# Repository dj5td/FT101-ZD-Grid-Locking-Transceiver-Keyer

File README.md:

# FT101-ZD-Grid-Locking-Transceiver-Keyer

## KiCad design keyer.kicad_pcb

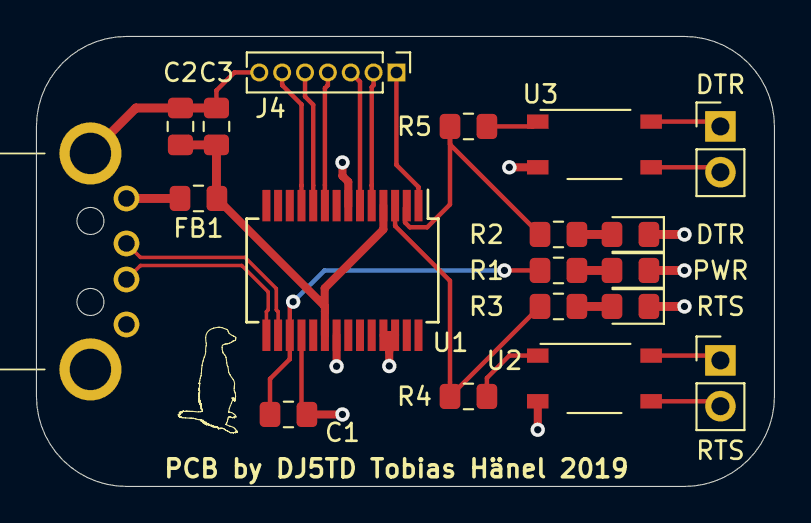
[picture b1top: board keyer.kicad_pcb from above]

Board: 2 copper layers, 41.0 x 25.0 mm, 19 parts (0 on the bottom side), 23 nets.

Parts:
C1, C2: 100nF; C_0805_2012Metric_Pad1.15x1.40mm_HandSolder
C3: 10 uF; C_0805_2012Metric_Pad1.15x1.40mm_HandSolder
DTR: LED; LED_0805_2012Metric_Pad1.15x1.40mm_HandSolder
DTR#2: Conn_Coaxial; PinHeader_1x02_P2.54mm_Vertical
FB1: Ferrite_Bead_Small; R_0805_2012Metric_Pad1.15x1.40mm_HandSolder
J1: USB_A; USB05
J4: Conn_01x06_Male; PinHeader_1x07_P1.27mm_Vertical
PWR: LED; LED_0805_2012Metric_Pad1.15x1.40mm_HandSolder
R1: 270R; R_0805_2012Metric_Pad1.15x1.40mm_HandSolder
R2, R3: 560R; R_0805_2012Metric_Pad1.15x1.40mm_HandSolder
R4, R5: 470; R_0805_2012Metric_Pad1.15x1.40mm_HandSolder
RTS: LED; LED_0805_2012Metric_Pad1.15x1.40mm_HandSolder
RTS#2: Conn_Coaxial; PinHeader_1x02_P2.54mm_Vertical
U1: FT232RL; SSOP-28_5.3x10.2mm_P0.65mm
U2, U3: TLP127; MFSOP6-4_4.4x3.6mm_P1.27mm

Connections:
+3V3: C1.2, R1.1, U1.17
/1: J4.1, U1.1
/5: J4.2, U1.5
/6: J4.3, U1.6
/9: J4.4, U1.9
/10: J4.5, U1.10
/11: J4.6, U1.11
/D+: J1.3, U1.15
/D-: J1.2, U1.16
/DTR: R2.1, R5.2, U1.2
/RTS: R3.1, R4.2, U1.3
GND: C1.1, C2.2, C3.2, DTR.1, J1.4, J1.5, J4.7, PWR.1, RTS.1, U1.7, U1.18, U1.21, U1.25, U1.26, U2.3, U3.3
unnamed: PWR.2, R1.2
unnamed: DTR.2, R2.2
unnamed: R3.2, RTS.2
unnamed: FB1.2, J1.1
unnamed: RTS#2.1, U2.6
unnamed: RTS#2.2, U2.4
unnamed: DTR#2.1, U3.6
unnamed: DTR#2.2, U3.4
unnamed: R4.1, U2.1
unnamed: R5.1, U3.1
VCC: C2.1, C3.1, FB1.1, U1.4, U1.20
